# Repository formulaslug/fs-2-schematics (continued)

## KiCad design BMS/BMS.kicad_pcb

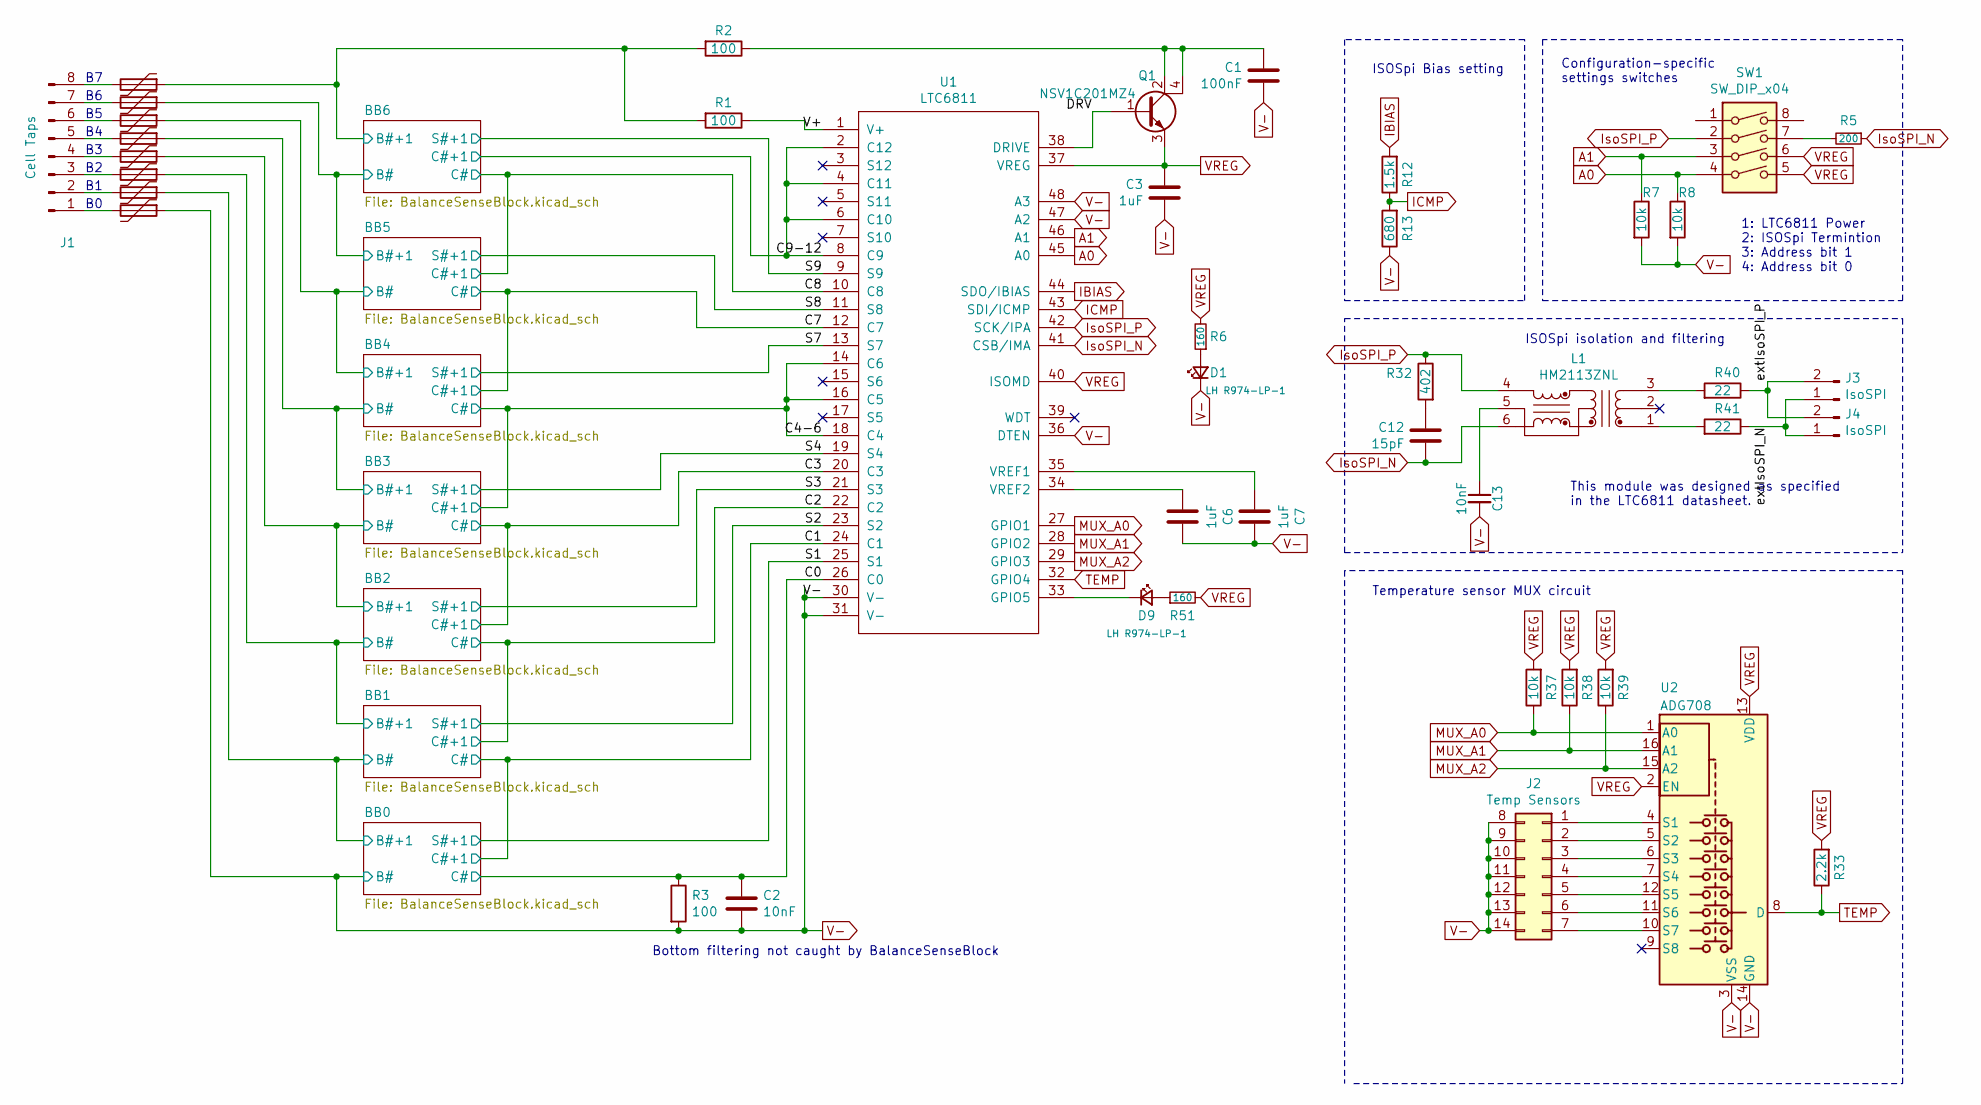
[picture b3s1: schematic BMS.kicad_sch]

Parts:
C1: 100nF; C_0805_2012Metric_Pad1.15x1.40mm_HandSolder
C2, C13: 10nF; C_0805_2012Metric_Pad1.15x1.40mm_HandSolder
C3, C6, C7: 1uF; C_0805_2012Metric_Pad1.15x1.40mm_HandSolder
C12: 15pF; C_0805_2012Metric_Pad1.15x1.40mm_HandSolder
D1, D9: LH R974-LP-1; LED_0805_2012Metric_Pad1.15x1.40mm_HandSolder
F1, F2, F3, F4, F5, F6, F7, F8: Polyfuse; Fuse_1812_4532Metric_Pad1.30x3.40mm_HandSolder
J1: Cell Taps; Molex_Nano-Fit_105313-xx08_1x08_P2.50mm_Horizontal
J2: Temp Sensors; Molex_Nano-Fit_105314-xx14_2x07_P2.50mm_Horizontal
J3, J4: IsoSPI; Molex_Nano-Fit_105313-xx02_1x02_P2.50mm_Horizontal
L1: HM2113ZNL
Q1: NSV1C201MZ4; SOT-223
R1, R2: 100; R_0805_2012Metric_Pad1.15x1.40mm_HandSolder
R3: 100; C_0805_2012Metric_Pad1.15x1.40mm_HandSolder
R5: 200; R_0805_2012Metric_Pad1.15x1.40mm_HandSolder
R6, R51: 160; R_0805_2012Metric_Pad1.15x1.40mm_HandSolder
R7, R8, R37, R38, R39: 10k; R_0805_2012Metric_Pad1.15x1.40mm_HandSolder
R12: 1.5k; R_0805_2012Metric_Pad1.15x1.40mm_HandSolder
R13: 680; R_0805_2012Metric_Pad1.15x1.40mm_HandSolder
R32: 402; R_0805_2012Metric_Pad1.15x1.40mm_HandSolder
R33: 2.2k; R_0805_2012Metric_Pad1.15x1.40mm_HandSolder
R40, R41: 22; R_0805_2012Metric_Pad1.15x1.40mm_HandSolder
SW1: SW_DIP_x04; DIP A6H-4101
U1: LTC6811; FSOP-48_[LTC6811-2]
U2: ADG708; TSSOP-16_4.4x5mm_P0.65mm

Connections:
/BB1/B#: F7.1; also elsewhere on the board
/BB2/B#: F6.1; also elsewhere on the board
/BB3/B#: F5.1; also elsewhere on the board
/BB4/B#: F4.1; also elsewhere on the board
/BB5/B#: F3.1; also elsewhere on the board
/BB6/B#: F2.1; also elsewhere on the board
/BB6/B#+1: F1.1, R1.2, R2.2; also elsewhere on the board
/C0: C2.1, R3.1, U1.26 (C0); also elsewhere on the board
/C1: U1.24 (C1); also elsewhere on the board
/C2: U1.22 (C2); also elsewhere on the board
/C3: U1.20 (C3); also elsewhere on the board
/C4-6: U1.14 (C6), U1.16 (C5), U1.18 (C4); also elsewhere on the board
/C7: U1.12 (C7); also elsewhere on the board
/C8: U1.10 (C8); also elsewhere on the board
/C9-12: U1.2 (C12), U1.4 (C11), U1.6 (C10), U1.8 (C9); also elsewhere on the board
/DRV: Q1.1 (B), U1.38 (DRIVE)
/S1: U1.25 (S1); also elsewhere on the board
/S2: U1.23 (S2); also elsewhere on the board
/S3: U1.21 (S3); also elsewhere on the board
/S4: U1.19 (S4); also elsewhere on the board
/S7: U1.13 (S7); also elsewhere on the board
/S8: U1.11 (S8); also elsewhere on the board
/S9: U1.9 (S9); also elsewhere on the board
/V+: R1.1, U1.1 (V+)
/extIsoSPI_N: J3.1, J4.1, R41.1
/extIsoSPI_P: J3.2, J4.2, R40.1
A0: R8.1, SW1.4, U1.45 (A0)
A1: R7.1, SW1.3, U1.46 (A1)
IBIAS: R12.2, U1.44 (SDO/IBIAS)
ICMP: R12.1, R13.2, U1.43 (SDI/ICMP)
IsoSPI_N: C12.1, L1.6, R5.1, U1.41 (CSB/IMA)
IsoSPI_P: L1.4, R32.1, SW1.2, U1.42 (SCK/IPA)
MUX_A0: R37.1, U1.27 (GPIO1), U2.1 (A0)
MUX_A1: R38.1, U1.28 (GPIO2), U2.16 (A1)
MUX_A2: R39.1, U1.29 (GPIO3), U2.15 (A2)
unnamed: C1.1, Q1.2 (C), Q1.4 (C), R2.1
unnamed: C6.2, U1.34 (VREF2)
unnamed: C7.2, U1.35 (VREF1)
unnamed: C12.2, R32.2
unnamed: C13.1, L1.5
unnamed: D1.2 (A), R6.1
unnamed: D9.1 (K), U1.33 (GPIO5)
unnamed: D9.2 (A), R51.1
unnamed: F1.2, J1.8
unnamed: F2.2, J1.7
unnamed: F3.2, J1.6
unnamed: F4.2, J1.5
unnamed: F5.2, J1.4
unnamed: F6.2, J1.3
unnamed: F7.2, J1.2
unnamed: F8.2, J1.1
unnamed: J2.1, U2.4 (S1)
unnamed: J2.2, U2.5 (S2)
unnamed: J2.3, U2.6 (S3)
unnamed: J2.4, U2.7 (S4)
unnamed: J2.5, U2.12 (S5)
unnamed: J2.6, U2.11 (S6)
unnamed: J2.7, U2.10 (S7)
unnamed: L1.1, R41.2
unnamed: L1.3, R40.2
unnamed: R5.2, SW1.7
TEMP: R33.1, U1.32 (GPIO4), U2.8 (D)
V-: C1.2, C2.2, C3.2, C6.1, C7.1, C13.2, D1.1 (K), F8.1, J2.8, J2.9, J2.10, J2.11, J2.12, J2.13, J2.14, R3.2, R7.2, R8.2, R13.1, U1.30 (V-), U1.31 (V-), U1.36 (DTEN), U1.47 (A2), U1.48 (A3), U2.3 (VSS), U2.14 (GND); also elsewhere on the board
VREG: C3.1, Q1.3 (E), R6.2, R33.2, R37.2, R38.2, R39.2, R51.2, SW1.5, SW1.6, U1.37 (VREG), U1.40 (ISOMD), U2.2 (EN), U2.13 (VDD)

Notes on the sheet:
ISOSpi Bias setting
This module was designed as specified in the LTC6811 datasheet.
Configuration-specific settings switches
1: LTC6811 Power 2: ISOSpi Termintion 3: Address bit 1 4: Address bit 0
Bottom filtering not caught by BalanceSenseBlock
Temperature sensor MUX circuit
ISOSpi isolation and filtering

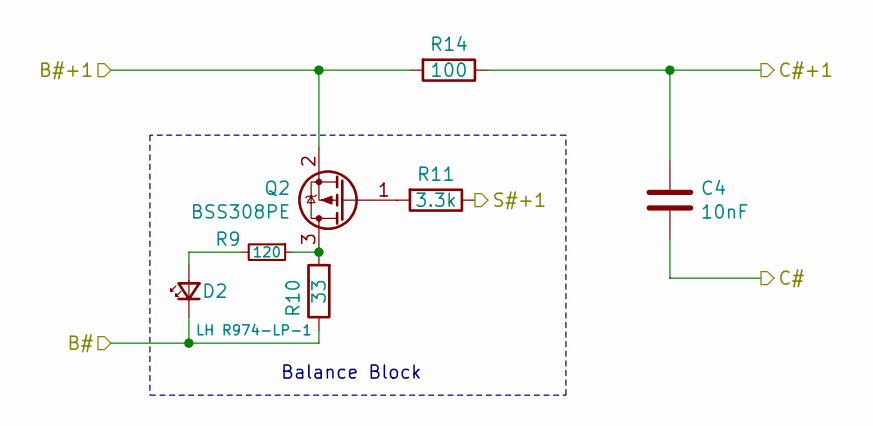
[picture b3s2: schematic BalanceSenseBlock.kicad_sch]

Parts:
C4: 10nF; C_0805_2012Metric_Pad1.15x1.40mm_HandSolder
D2: LH R974-LP-1; LED_0805_2012Metric_Pad1.15x1.40mm_HandSolder
Q2: BSS308PE; SOT-23
R9: 120; R_0805_2012Metric_Pad1.15x1.40mm_HandSolder
R10: 33; R_2512_6332Metric_Pad1.52x3.35mm_HandSolder
R11: 3.3k; R_0805_2012Metric_Pad1.15x1.40mm_HandSolder
R14: 100; R_0805_2012Metric_Pad1.15x1.40mm_HandSolder

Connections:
/BB6/B#: D2.1 (K), R10.1; also elsewhere on the board
/BB6/B#+1: Q2.2 (S), R14.2; also elsewhere on the board
/C8: C4.2; also elsewhere on the board
/C9-12: C4.1, R14.1; also elsewhere on the board
/S9: R11.1; also elsewhere on the board
unnamed: D2.2 (A), R9.2
unnamed: Q2.1 (G), R11.2
unnamed: Q2.3 (D), R9.1, R10.2

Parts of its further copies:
C5, C8, C9, C10, C11, C14: 10nF; C_0805_2012Metric_Pad1.15x1.40mm_HandSolder
D3, D4, D5, D6, D7, D8: LH R974-LP-1; LED_0805_2012Metric_Pad1.15x1.40mm_HandSolder
Q3, Q4, Q5, Q6, Q7, Q8: BSS308PE; SOT-23
R15, R19, R23, R27, R31, R42: 120; R_0805_2012Metric_Pad1.15x1.40mm_HandSolder
R16, R20, R24, R28, R34, R43: 33; R_2512_6332Metric_Pad1.52x3.35mm_HandSolder
R17, R21, R25, R29, R35, R44: 3.3k; R_0805_2012Metric_Pad1.15x1.40mm_HandSolder
R18, R22, R26, R30, R36, R45: 100; R_0805_2012Metric_Pad1.15x1.40mm_HandSolder

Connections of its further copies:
/BB1/B#: D7.1 (K), Q8.2 (S), R34.1, R45.2; also elsewhere on the board
/BB2/B#: D6.1 (K), Q7.2 (S), R28.1, R36.2; also elsewhere on the board
/BB3/B#: D5.1 (K), Q6.2 (S), R24.1, R30.2; also elsewhere on the board
/BB4/B#: D4.1 (K), Q5.2 (S), R20.1, R26.2; also elsewhere on the board
/BB5/B#: D3.1 (K), Q4.2 (S), R16.1, R22.2; also elsewhere on the board
/BB6/B#: Q3.2 (S), R18.2; also elsewhere on the board
/C0: C14.2; also elsewhere on the board
/C1: C11.2, C14.1, R45.1; also elsewhere on the board
/C2: C10.2, C11.1, R36.1; also elsewhere on the board
/C3: C9.2, C10.1, R30.1; also elsewhere on the board
/C4-6: C8.2, C9.1, R26.1; also elsewhere on the board
/C7: C5.2, C8.1, R22.1; also elsewhere on the board
/C8: C5.1, R18.1; also elsewhere on the board
/S1: R44.1; also elsewhere on the board
/S2: R35.1; also elsewhere on the board
/S3: R29.1; also elsewhere on the board
/S4: R25.1; also elsewhere on the board
/S7: R21.1; also elsewhere on the board
/S8: R17.1; also elsewhere on the board
unnamed: D3.2 (A), R15.2
unnamed: D4.2 (A), R19.2
unnamed: D5.2 (A), R23.2
unnamed: D6.2 (A), R27.2
unnamed: D7.2 (A), R31.2
unnamed: D8.2 (A), R42.2
unnamed: Q3.1 (G), R17.2
unnamed: Q3.3 (D), R15.1, R16.2
unnamed: Q4.1 (G), R21.2
unnamed: Q4.3 (D), R19.1, R20.2
unnamed: Q5.1 (G), R25.2
unnamed: Q5.3 (D), R23.1, R24.2
unnamed: Q6.1 (G), R29.2
unnamed: Q6.3 (D), R27.1, R28.2
unnamed: Q7.1 (G), R35.2
unnamed: Q7.3 (D), R31.1, R34.2
unnamed: Q8.1 (G), R44.2
unnamed: Q8.3 (D), R42.1, R43.2
V-: D8.1 (K), R43.1; also elsewhere on the board

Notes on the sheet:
Balance Block

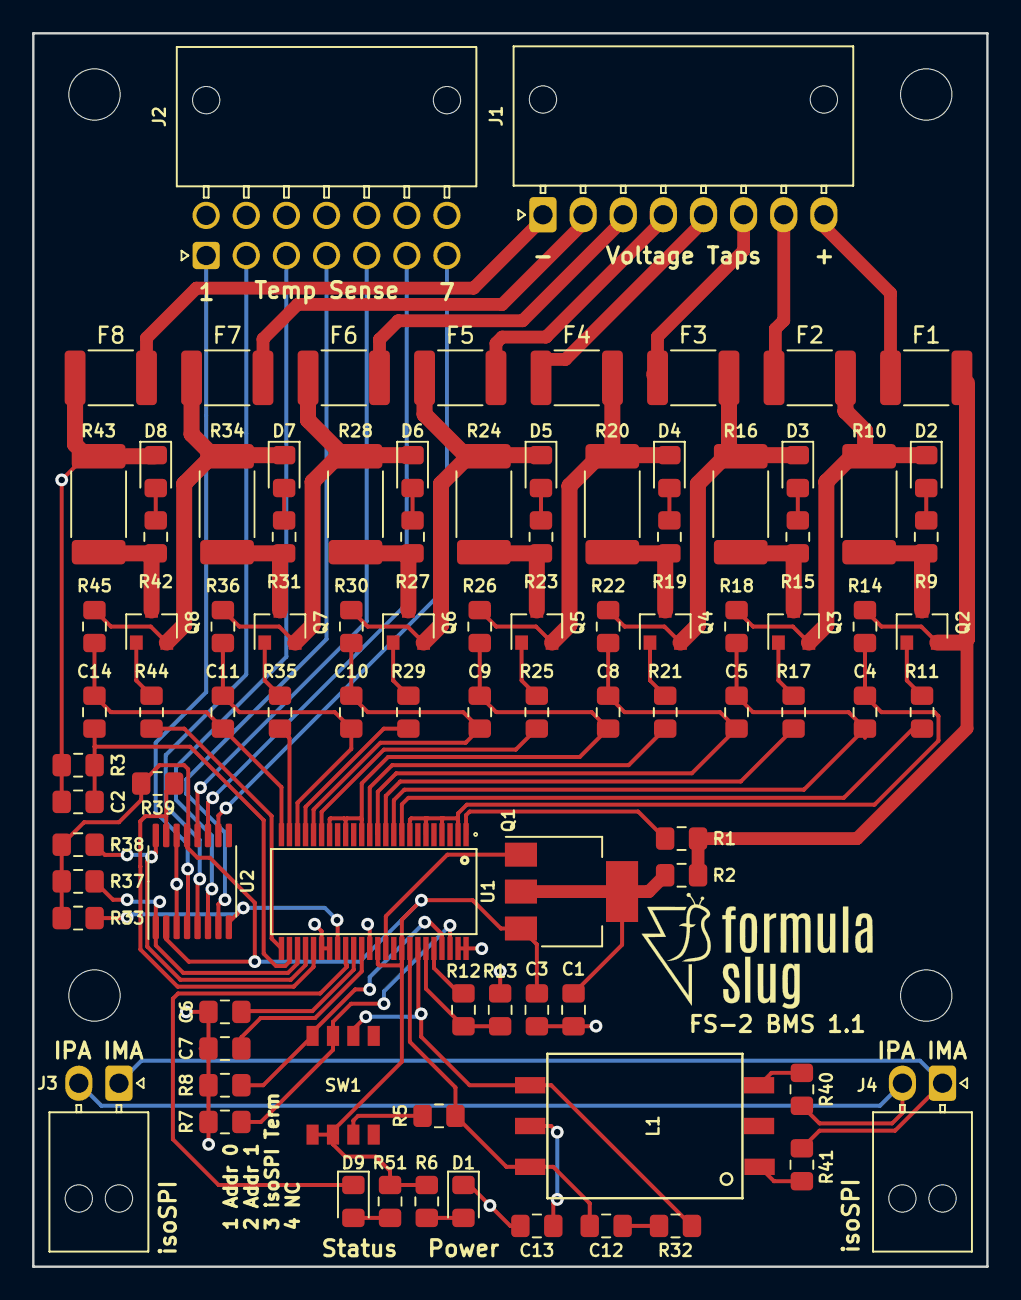
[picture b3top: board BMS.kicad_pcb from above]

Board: 2 copper layers, 59.4 x 76.8 mm, 92 parts (0 on the bottom side), 85 nets.

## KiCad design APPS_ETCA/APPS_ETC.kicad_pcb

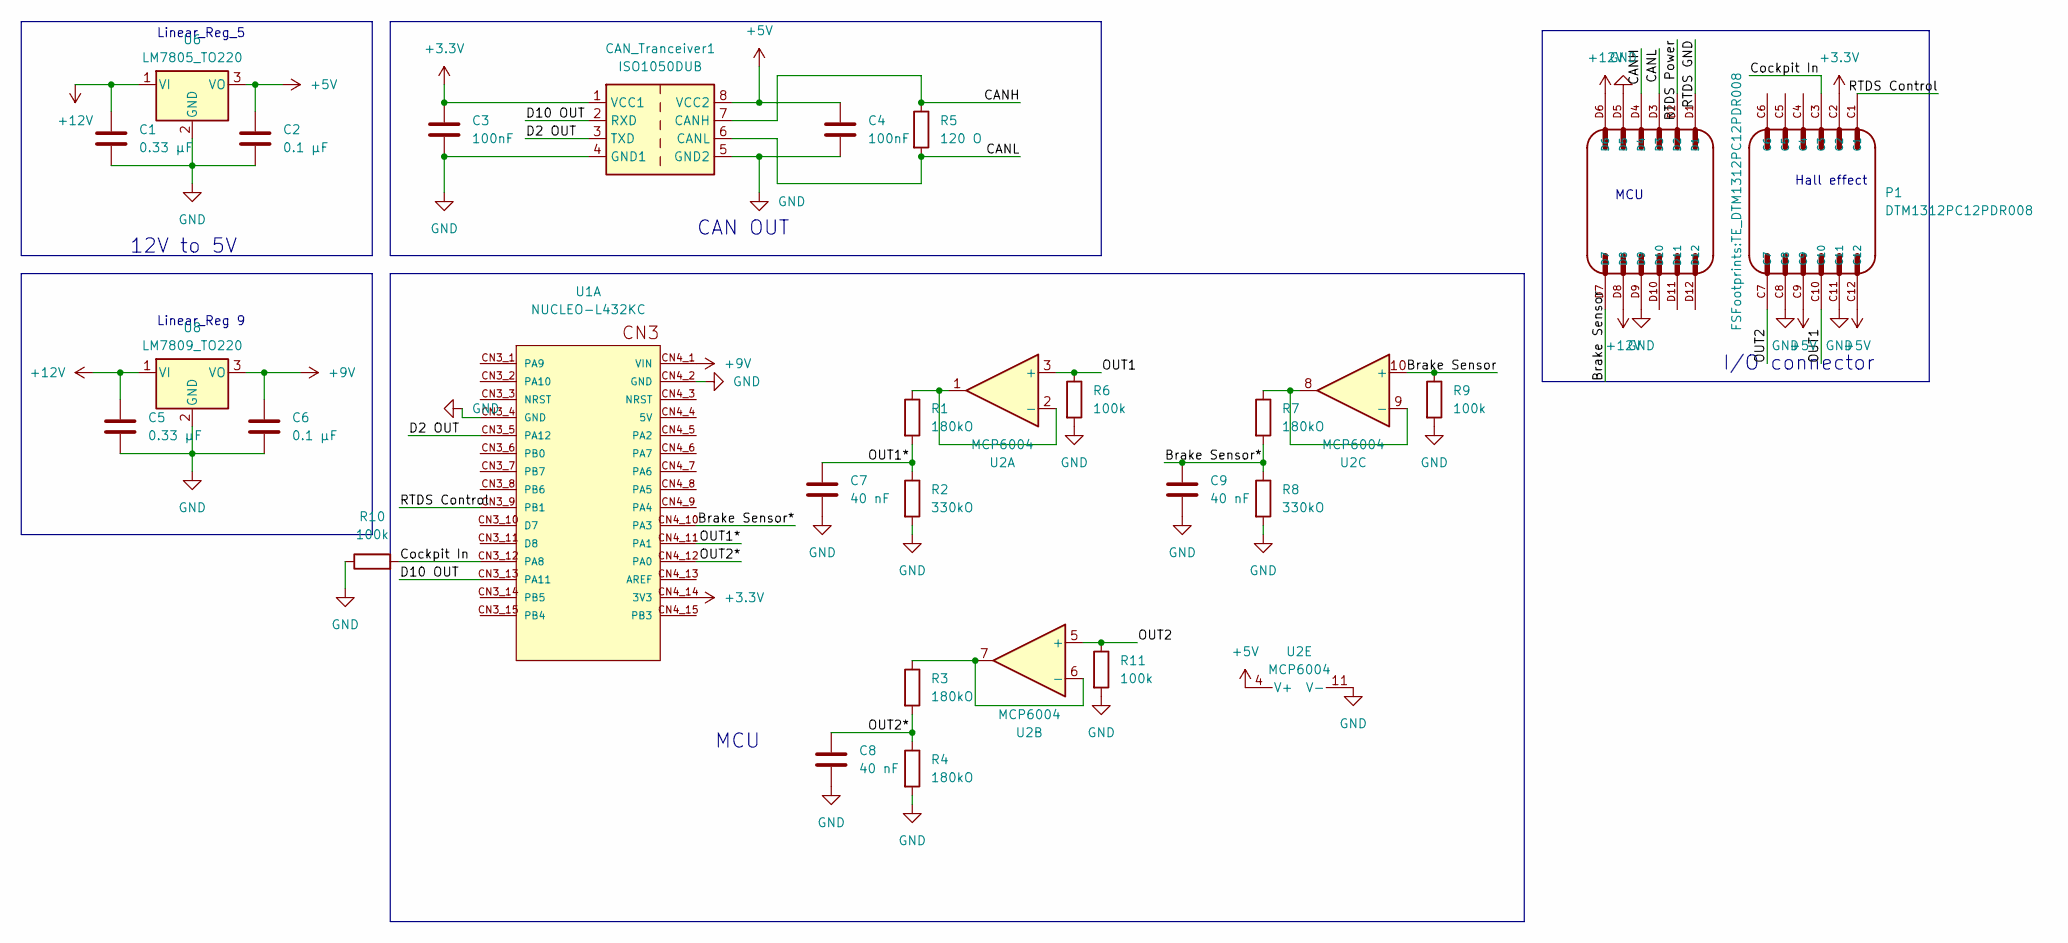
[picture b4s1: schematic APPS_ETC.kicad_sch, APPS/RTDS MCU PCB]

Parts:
C1, C5: 0.33 µF; C_0805_2012Metric_Pad1.18x1.45mm_HandSolder
C2, C6: 0.1 µF; C_0805_2012Metric_Pad1.18x1.45mm_HandSolder
C3, C4: 100nF; C_0805_2012Metric_Pad1.18x1.45mm_HandSolder
C7, C8, C9: 40 nF; C_0805_2012Metric_Pad1.18x1.45mm_HandSolder
CAN_Tranceiver1: ISO1050DUB; SOP-8_6.62x9.15mm_P2.54mm
P1: DTM1312PC12PDR008; TE_DTM1312PC12PDR008
R1, R3, R4, R7: 180kO; R_0805_2012Metric_Pad1.20x1.40mm_HandSolder
R2, R8: 330kO; R_0805_2012Metric_Pad1.20x1.40mm_HandSolder
R5: 120 O; R_0805_2012Metric_Pad1.20x1.40mm_HandSolder
R6, R9, R10, R11: 100k; R_0805_2012Metric_Pad1.20x1.40mm_HandSolder
U1: NUCLEO-L432KC; MODULE_NUCLEO-L432KC; PARTREV N/A
U2: MCP6004; PDIP14_300MC_MCH
U6: LM7805_TO220; TO-220-3_Vertical
U8: LM7809_TO220; TO-220-3_Vertical

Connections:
+3.3V: C3.1, CAN_Tranceiver1.1 (VCC1), P1.C2, U1.CN4_14 (3V3)
+5V: C2.1, C4.1, CAN_Tranceiver1.8 (VCC2), P1.C9, P1.C12, U2.4 (V+), U6.3 (VO)
+9V: C6.1, U1.CN4_1 (VIN), U8.3 (VO)
+12V: C1.1, C5.1, P1.D6, P1.D8, U6.1 (VI), U8.1 (VI)
/Brake Sensor: P1.D7, R9.1, U2.10 (+)
/Brake Sensor*: C9.1, R7.2, R8.1, U1.CN4_10 (PA3)
/CANH: CAN_Tranceiver1.7 (CANH), P1.D4, R5.1
/CANL: CAN_Tranceiver1.6 (CANL), P1.D3, R5.2
/Cockpit In: P1.C3, R10.2, U1.CN3_12 (PA8)
/D2 OUT: CAN_Tranceiver1.3 (TXD), U1.CN3_5 (PA12)
/D10 OUT: CAN_Tranceiver1.2 (RXD), U1.CN3_13 (PA11)
/OUT1: P1.C10, R6.1, U2.3 (+)
/OUT1*: C7.1, R1.2, R2.1, U1.CN4_11 (PA1)
/OUT2: P1.C7, R11.1, U2.5 (+)
/OUT2*: C8.1, R3.2, R4.1, U1.CN4_12 (PA0)
/RTDS Control: P1.C1, U1.CN3_9 (PB1)
/RTDS GND: P1.D1
/RTDS Power: P1.D2
GND: C1.2, C2.2, C3.2, C4.2, C5.2, C6.2, C7.2, C8.2, C9.2, CAN_Tranceiver1.4 (GND1), CAN_Tranceiver1.5 (GND2), P1.C8, P1.C11, P1.D5, P1.D9, R2.2, R4.2, R6.2, R8.2, R9.2, R10.1, R11.2, U1.CN3_4 (GND), U1.CN4_2 (GND), U2.11 (V-), U6.2 (GND), U8.2 (GND)
unnamed: R1.1, U2.1, U2.2 (-)
unnamed: R3.1, U2.6 (-), U2.7
unnamed: R7.1, U2.8, U2.9 (-)

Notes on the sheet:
Linear_Reg_5
I/O connector
12V to 5V
Hall effect
CAN OUT
MCU
Linear_Reg 9

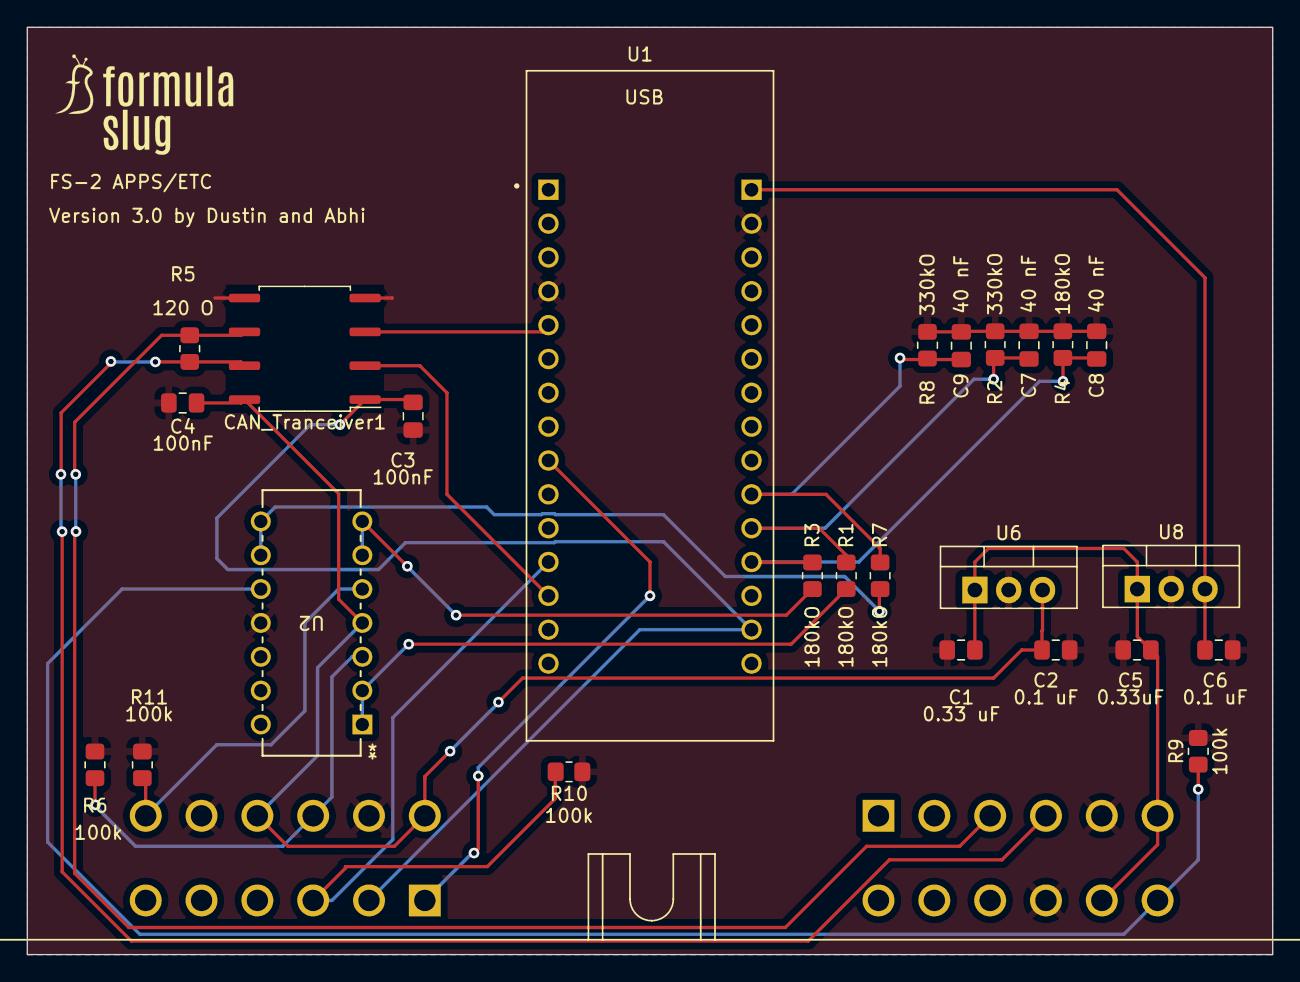
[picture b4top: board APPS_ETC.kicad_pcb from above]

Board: 2 copper layers, 93.5 x 69.6 mm, 26 parts (0 on the bottom side), 20 nets.

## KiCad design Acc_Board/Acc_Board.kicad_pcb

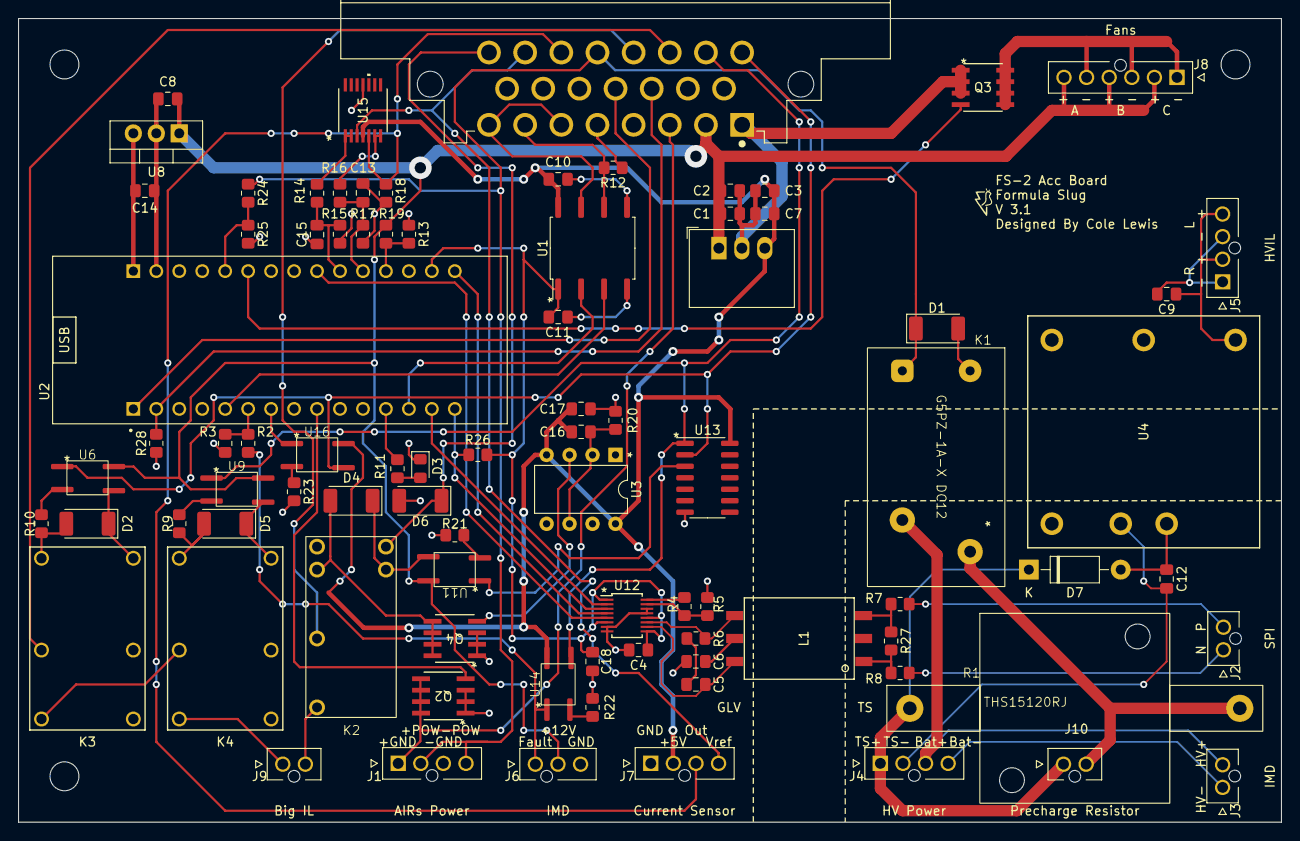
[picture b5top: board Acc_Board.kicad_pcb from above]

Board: 2 copper layers, 139.7 x 88.9 mm, 86 parts (0 on the bottom side), 71 nets.

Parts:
C1, C7, C9: 10µF; C_0805_2012Metric_Pad1.18x1.45mm_HandSolder
C2, C3, C4, C10, C11, C18: 100nF; C_0805_2012Metric_Pad1.18x1.45mm_HandSolder
C5: 15pF; C_0805_2012Metric_Pad1.18x1.45mm_HandSolder
C6: 10nF; C_0805_2012Metric_Pad1.18x1.45mm_HandSolder
C8, C14: 330nF; C_0805_2012Metric_Pad1.18x1.45mm_HandSolder
C12: 1µF; C_0805_2012Metric_Pad1.18x1.45mm_HandSolder
C13, C15: C; C_0805_2012Metric_Pad1.18x1.45mm_HandSolder
C16: 1uf; C_0805_2012Metric_Pad1.18x1.45mm_HandSolder
C17: 100nf; C_0805_2012Metric_Pad1.18x1.45mm_HandSolder
D1, D2, D4, D5, D6: D; D_2010_5025Metric_Pad1.52x2.65mm_HandSolder
D3: LED; LED_0805_2012Metric_Pad1.15x1.40mm_HandSolder
D7: 1N47xxA; D_DO-41_SOD81_P10.16mm_Horizontal
J1: AIRs Power; MOLEX_1053091204
J2: IsoSPI; MOLEX_1053091202
J3: IMD BAT; MOLEX_1053091202
J4: HV Power; MOLEX_1053091204
J5: HVIL; MOLEX_1053091204
J6: IMD; MOLEX_1053091203
J7: Current Sensor; MOLEX_1053091204
J8: Fans; MOLEX_1053091206
J9: Shutdown IL; MOLEX_1053091202
J10: Precharge Resistor; MOLEX_1053091202
J12: 776087-1; TE_776087-1
K1: G5PZ-1A-X DC12
K2: G6BK-1114P-US; Omron G6BK-1114P-US
K3, K4: DK1A1B-12V; RELAY_DK2A_PAN
L1: HM2113ZNL
Q2, Q3, Q4: STS6NF20V; SO-8_STM
R1: 120; THS15120RJ
R2: 1.6k; R_0805_2012Metric_Pad1.20x1.40mm_HandSolder
R3: 560; R_0805_2012Metric_Pad1.20x1.40mm_HandSolder
R4: 1.5k; R_0805_2012Metric_Pad1.20x1.40mm_HandSolder
R5: 680; R_0805_2012Metric_Pad1.20x1.40mm_HandSolder
R6: 402; R_0805_2012Metric_Pad1.20x1.40mm_HandSolder
R7, R8: 22; R_0805_2012Metric_Pad1.20x1.40mm_HandSolder
R9, R10, R21: 374; R_0805_2012Metric_Pad1.20x1.40mm_HandSolder
R11, R12: 120; R_0805_2012Metric_Pad1.20x1.40mm_HandSolder
R13: 3.9k; R_0805_2012Metric_Pad1.20x1.40mm_HandSolder
R14, R16: 1k; R_0805_2012Metric_Pad1.20x1.40mm_HandSolder
R15, R17: 2k; R_0805_2012Metric_Pad1.20x1.40mm_HandSolder
R18, R28: 10k; R_0805_2012Metric_Pad1.20x1.40mm_HandSolder
R19: 18k; R_0805_2012Metric_Pad1.20x1.40mm_HandSolder
R20: 2.4M; R_0805_2012Metric_Pad1.20x1.40mm_HandSolder
R22: 665; R_0805_2012Metric_Pad1.20x1.40mm_HandSolder
R23: 205; R_0805_2012Metric_Pad1.20x1.40mm_HandSolder
R24: 22k; R_0805_2012Metric_Pad1.20x1.40mm_HandSolder
R25: 6.8K; R_0805_2012Metric_Pad1.20x1.40mm_HandSolder
R26: 2.2k; R_0805_2012Metric_Pad1.20x1.40mm_HandSolder
R27: 200; R_0805_2012Metric_Pad1.20x1.40mm_HandSolder
U1: ISO1050DUB; SOP-8_6.62x9.15mm_P2.54mm
U2: NUCLEO-L432KC; MODULE_NUCLEO-L432KC
U3: LM555N; DIP-8_W7.62mm
U4: PQDE6W-Q110-S5-H-D; PQDE6W-Q110-S5-H-D_CUI
U5: R-78B5.0-2.0; Converter_DCDC_RECOM_R-78B-2.0_THT
U6, U9, U11, U14, U16: TLP3122AE; OptoCoupler 6-SOP
U8: LM7809_TO220; TO-220-3_Vertical
U12: LTC6820; MSOP-16_[LTC6820]_10_thou_compat
U13: HEF4093B; SOIC-14_3.9x8.7mm_P1.27mm
U15: MCP6004; TSSOP14_MC_MCH

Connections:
+3.3V: C4.1, C11.2, C18.1, R26.2, U1.1 (VCC1), U2.CN4_14 (3V3), U12.1 (EN), U12.6 (V_DDS), U12.9 (V_DD), U12.12 (MSTR)
+5V: C3.1, C7.1, C10.2, C16.1, C17.2, J7.2, U1.8 (VCC2), U3.4 (R), U3.8 (VCC), U5.3 (OUT), U13.14 (VCC), U14.6, U15.4 (V+), U16.6
+9V: C14.1, U2.CN4_1 (VIN), U8.3 (VO)
+12V: C1.1, C2.1, C8.1, J6.2, J8.2, J8.4, J8.6, J12.2, R19.2, U5.1 (IN), U6.6, U8.1 (VI), U9.6, U11.6
/AIRS+_12V: D1.1 (K), J1.2, J1.4, J12.20, K1.1, R24.1
/AIRS+_GND: J1.1, J12.3, Q2.5 (D), Q2.6 (D), Q2.7 (D), Q2.8 (D)
/BAT+: J3.2, J4.3, K1.2
/BAT-: J3.1, J4.4
/BMS_FAULT: U2.CN3_7 (PB7), U16.1
/BMS_FAULT_5V: J12.16, U6.1, U13.2, U16.4
/Buffered_C_Out: C13.1, R16.1, R17.2, U2.CN4_11 (PA1)
/Buffered_C_Vref: C15.2, R14.1, R15.2, U2.CN4_10 (PA3)
/CAN1_RD: U1.2 (RXD), U2.CN3_13 (PA11)
/CAN1_TD: U1.3 (TXD), U2.CN3_5 (PA12)
/CAN_H: J12.6, J12.8, U1.7 (CANH)
/CAN_L: J12.7, R12.2, U1.6 (CANL)
/CAN_L_RES: J12.5, R12.1
/Charge_Enable: J12.12, U2.CN3_1 (PA9)
/Charge_State: J12.11, R28.2, U2.CN3_2 (PA10)
/Current_Output: J7.3, J12.21, R18.1, U15.5 (+)
/Current_Vref: J7.4, J12.22, U15.3 (+)
/Fan_Control: Q3.4 (G), U2.CN4_6 (PA7)
/GLV Voltage: R13.2, R19.1, U2.CN4_12 (PA0)
/HVIL+: C9.1, J5.2, J5.4, U4.4
/IMD_FAULT: J6.1, R2.2, U14.1
/IMD_FAULT_5V: J12.17, U9.1, U13.1, U14.4
/IMD_Latch_Delay: Q4.4 (G), U3.3 (Q)
/IMD_Status: R2.1, R3.2, U2.CN3_6 (PB0)
/Iso SPI/IBIAS: R4.2, U12.16 (IBIAS)
/Iso SPI/ICMP: R4.1, R5.2, U12.15 (ICMP)
/Iso SPI/STM_MISO: R26.1, U2.CN3_15 (PB4), U12.3 (MISO)
/Iso SPI/STM_MOSI: U2.CN3_14 (PB5), U12.2 (MOSI)
/Iso SPI/STM_NSS: U2.CN4_9 (PA4), U12.5 (CS)
/Iso SPI/STM_SCK: U2.CN4_15 (PB3), U12.4 (SCK)
/Iso SPI/extIsoSPI_N: J2.1, R8.1
/Iso SPI/extIsoSPI_P: J2.2, R7.1
/Iso SPI/isoSPI_+: L1.4, R6.1, U12.11 (IP)
/Iso SPI/isoSPI_-: C5.1, L1.6, U12.10 (IM)
/Precharge_Control: Q2.4 (G), U2.CN3_9 (PB1)
/SH_RESET: D6.1 (K), J12.23, K2.6
/Shutdown_ACC_IN: J12.18, K3.3
/Shutdown_ACC_OUT: J12.19, K2.3
/Shutdown_Measure: R24.2, R25.1, U2.CN4_5 (PA2)
/TS+: D7.1 (K), J4.1, J10.1, R1.+
/TS-: C12.2, J4.2, U4.2
GND: C1.2, C2.2, C3.2, C4.2, C6.2, C7.2, C8.2, C9.2, C10.1, C11.1, C13.2, C14.2, C15.1, C17.1, C18.2, D1.2 (A), D2.2 (A), D3.1 (K), D5.2 (A), D6.2 (A), J1.3, J5.1, J5.3, J6.3, J7.1, J12.1, K1.4, K2.1, K3.1 (-), K4.1 (-), Q2.1 (S), Q2.2 (S), Q2.3 (S), Q3.1 (S), Q3.2 (S), Q3.3 (S), Q4.1 (S), Q4.2 (S), Q4.3 (S), R3.1, R5.1, R9.1, R10.2, R13.1, R15.1, R17.1, R18.2, R20.2, R21.2, R22.2, R23.2, R25.2, R28.1, U1.4 (GND1), U1.5 (GND2), U2.CN3_4 (GND), U2.CN4_2 (GND), U3.1 (GND), U4.6, U5.2 (GND), U8.2 (GND), U12.7 (POL), U12.8 (PHA), U12.13 (SLOW), U12.14 (GND), U13.7 (GND), U15.11 (V-)
unnamed: C5.2, R6.2
unnamed: C6.1, L1.5
unnamed: D2.1 (K), K3.8 (+), U6.4
unnamed: D3.2 (A), R11.1
unnamed: D4.2 (A), K2.2, Q4.5 (D), Q4.6 (D), Q4.7 (D), Q4.8 (D)
unnamed: D4.1 (K), K2.5, U11.4
unnamed: D5.1 (K), K4.8 (+), U9.4
unnamed: C12.1, D7.2 (A), U4.3
unnamed: J8.1, J8.3, J8.5, Q3.5 (D), Q3.6 (D), Q3.7 (D), Q3.8 (D)
unnamed: J9.1, K4.4
unnamed: J9.2, K2.4
unnamed: J10.2, K1.3, R1.-
unnamed: K3.4, K4.3
unnamed: L1.1, R8.2, R27.2
unnamed: L1.3, R7.2, R27.1
unnamed: R9.2, U9.3
unnamed: R10.1, U6.3
unnamed: R21.1, U11.3
unnamed: R22.1, U14.3
unnamed: R23.1, U16.3
unnamed: R11.2, U2.CN3_12 (PA8)
unnamed: C16.2, R20.1, U3.2 (TR), U3.6 (THR)
unnamed: U11.1, U13.3
unnamed: R14.2, U15.1, U15.2 (-)
unnamed: R16.2, U15.6 (-), U15.7

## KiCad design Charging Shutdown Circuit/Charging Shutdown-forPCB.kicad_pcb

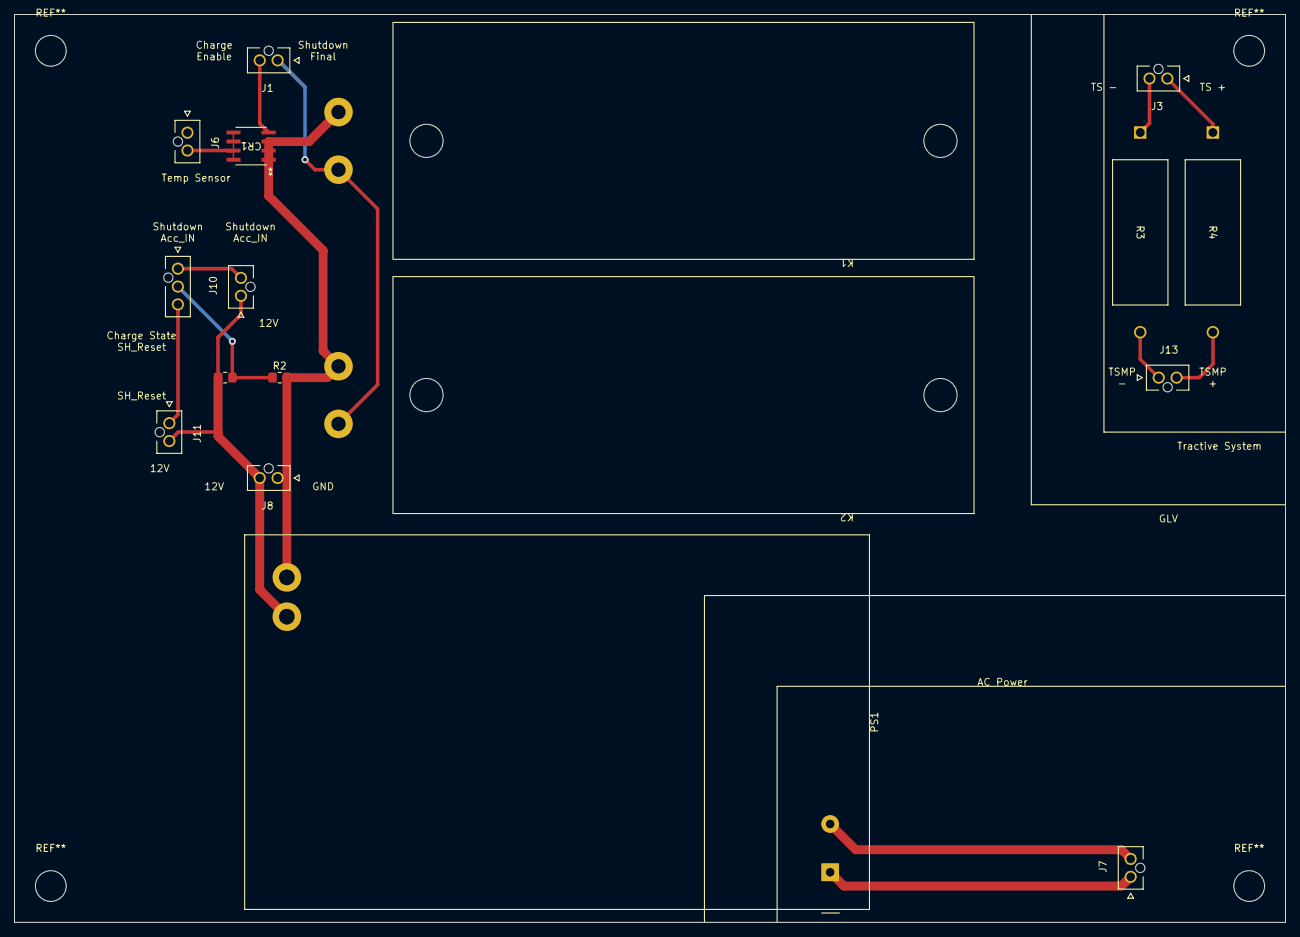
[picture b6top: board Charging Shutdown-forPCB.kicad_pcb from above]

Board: 2 copper layers, 177.8 x 127.0 mm, 17 parts (0 on the bottom side), 14 nets.

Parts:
CR1: N-MOS; SO-8_STM
J1: in charger; MOLEX_1053091202
J3: 120v DC (in); MOLEX_1053091202
J4: Out of Charger; MOLEX_1053091203
J6: Temp Sensor; MOLEX_1053091202
J7: AC in this world!; MOLEX_1053091202
J8: DC out of this world!; MOLEX_1053091202
J10: Button E-STOP; MOLEX_1053091202
J11: SH-RESET; MOLEX_1053091202
J13: TSMP (out); MOLEX_1053091202
K1: Charger Contactor +; GIGAVAC P115BDA
K2: Charger Contactor -; GIGAVAC P115BDA
PS1: 120vAC to 12v DC; Converter_ACDC_MeanWell_IRM-60-xx_THT
R1: 18k; R_0805_2012Metric_Pad1.20x1.40mm_HandSolder
R2: 6.8k; R_0805_2012Metric_Pad1.20x1.40mm_HandSolder
R3, R4: 5k; RES_WH&slash_NE_OHM

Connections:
+12V: J8.2, J10.1, J11.2, PS1.4 (+Vout), R1.1
/120AC /L: J7.1, PS1.1 (AC/L)
/120AC /N: J7.2, PS1.2 (AC/N)
/Charge_Enable: CR1.4 (G), J1.2
/Charge_State: J4.2, R1.2, R2.1
/SH_RESET: J4.3, J11.1
/Shutdown_ACC_IN: J4.1, J10.2
/Shutdown_Final: J1.1, K1.4 (X2), K2.4 (X2)
/Temperature Sensor: CR1.5 (D), CR1.6 (D), CR1.7 (D), CR1.8 (D), J6.2
GND: CR1.1 (S), CR1.2 (S), CR1.3 (S), J8.1, K1.3 (X1), K2.3 (X1), PS1.3 (-Vout), R2.2
unnamed: J3.1, R4.1
unnamed: J3.2, R3.1
unnamed: J13.1, R3.2
unnamed: J13.2, R4.2

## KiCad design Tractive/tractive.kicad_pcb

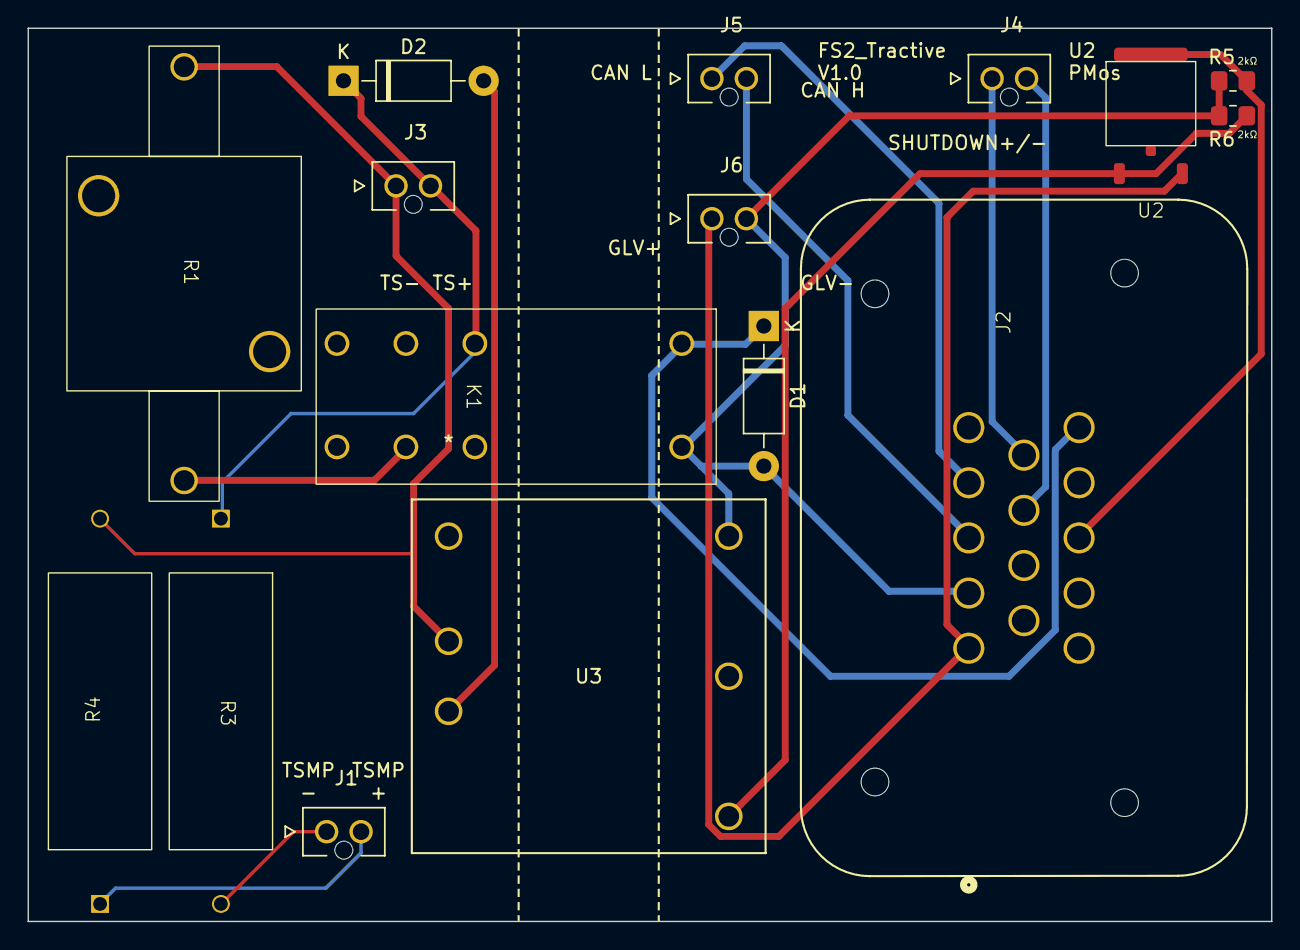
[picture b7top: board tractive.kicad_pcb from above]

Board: 2 copper layers, 90.2 x 64.8 mm, 16 parts (0 on the bottom side), 15 nets.

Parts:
D1: 1N4001; D_DO-41_SOD81_P10.16mm_Horizontal
D2: 20; D_DO-41_SOD81_P10.16mm_Horizontal
J1, J3: TS; MOLEX_1053091202
J2: 776261-1; CONN14_776261_TEC
J4: Shutdown; MOLEX_1053091202
J5: CAN; MOLEX_1053091202
J6: GLV; MOLEX_1053091202
K1: PhoenixContact; PhoenixContact1
R1: 680; Discharge Resistor
R3, R4: 5k; TSMP Resistor
R5, R6: 2k; R_0805_2012Metric_Pad1.20x1.40mm_HandSolder
U2: PMos
U3: PQDE6W-Q110-S5-H-D; PQDE6W-Q110-S5-H-D_CUI

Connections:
/AIRS_FINAL: D1.1 (K), J2.14, K1.1 (coil)
GND: D1.2 (A), J2.2, J6.2, K1.2 (coil), R5.1, R6.2, U3.6
unnamed: D2.2 (A), U3.3
unnamed: D2.1 (K), J3.2, K1.3, R3.1
unnamed: J1.1, R3.2
unnamed: J1.2, R4.1
unnamed: J2.3, J5.2
unnamed: J2.4, J5.1
unnamed: J2.8, J4.2
unnamed: J2.9, J4.1
unnamed: J3.1, R1.2, R4.2, U3.2
unnamed: K1.4 (switching), R1.1
unnamed: J2.12, R6.1, U2.3 (D)
unnamed: R5.2, U2.1 (G), U3.4
unnamed: J2.1, J6.1, U2.2 (S)
